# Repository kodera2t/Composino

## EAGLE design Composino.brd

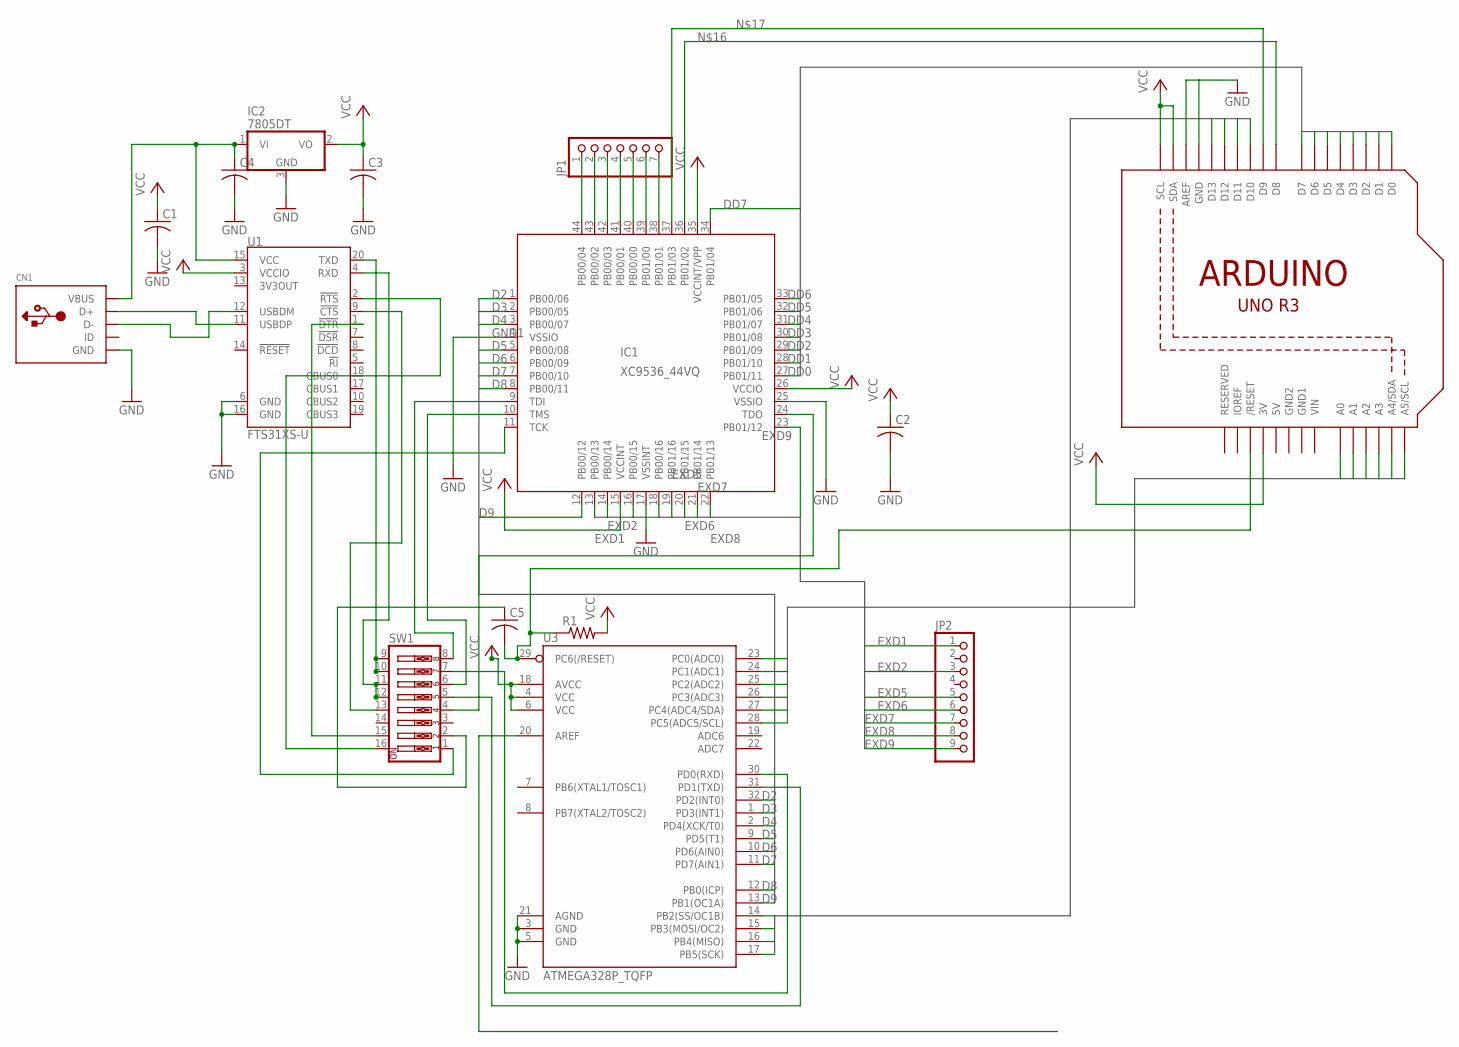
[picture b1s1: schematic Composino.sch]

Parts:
C1, C2, C3, C4, C5: C-USC0603K; C0603K
CN1: USBMINIBLARGE; USB-MINIB_LARGER
IC1: XC9536_44VQ; SQFP-S-10X10-44
IC2: 7805DT; TO252
JP1: HEADER-1X7; 1X07_OVAL
JP2: HEADER-1X9; 1X09_OVAL
R1: R-US_R0603; R0603
SW1: SW_DIP-8-SMT-HALFSIZE; DIPSWITCH-08-50MIL
U1: FTS31XS-U; SSOP20_L
U2: ARDUINOR3NODIM; ARDUINOR3-NODIM
U3: ATMEGA328P_TQFP; TQFP32-08

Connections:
5V: U2.5V
A0: U2.A0, U3.23 (PC0(ADC0))
A1: U2.A1, U3.24 (PC1(ADC1))
A2: U2.A2, U3.25 (PC2(ADC2))
A3: U2.A3, U3.26 (PC3(ADC3))
A4: U2.A4 (A4/SDA), U3.27 (PC4(ADC4/SDA))
A5: U2.A5 (A5/SCL), U3.28 (PC5(ADC5/SCL))
D2: IC1.1 (PB00/06), U3.32 (PD2(INT0))
D3: IC1.2 (PB00/05), U3.1 (PD3(INT1))
D4: IC1.3 (PB00/07), U3.2 (PD4(XCK/T0))
D5: IC1.5 (PB00/08), U3.9 (PD5(T1))
D6: IC1.6 (PB00/09), U3.10 (PD6(AIN0))
D7: IC1.7 (PB00/10), U3.11 (PD7(AIN1))
D8: IC1.8 (PB00/11), U3.12 (PB0(ICP))
D9: IC1.12 (PB00/12), U3.13 (PB1(OC1A))
D10: U2.D10, U3.14 (PB2(SS/OC1B))
D11: U2.D11, U3.15 (PB3(MOSI/OC2))
D12: U2.D12, U3.16 (PB4(MISO))
D13: U2.D13, U3.17 (PB5(SCK))
DD0: IC1.27 (PB01/11), U2.D0
DD1: IC1.28 (PB01/10), U2.D1
DD2: IC1.29 (PB01/09), U2.D2
DD3: IC1.30 (PB01/08), U2.D3
DD4: IC1.31 (PB01/07), U2.D4
DD5: IC1.32 (PB01/06), U2.D5
DD6: IC1.33 (PB01/05), U2.D6
DD7: IC1.34 (PB01/04), U2.D7
EXD1: IC1.13 (PB00/13), JP2.1
EXD2: IC1.14 (PB00/14), JP2.3
EXD3: IC1.16 (PB00/15)
EXD4: IC1.18 (PB00/16)
EXD5: IC1.19 (PB01/16), JP2.5
EXD6: IC1.20 (PB01/15), JP2.6
EXD7: IC1.21 (PB01/14), JP2.7
EXD8: IC1.22 (PB01/13), JP2.8
EXD9: IC1.23 (PB01/12), JP2.9
GND1: C1.2, C2.2, C3.2, C4.2, CN1.GND, IC1.4 (VSSIO), IC1.17 (VSSINT), IC1.25 (VSSIO), IC2.3 (GND), U1.6 (GND), U1.16 (GND), U2.AREF, U2.GND, U2.GND1, U2.GND2, U3.3 (GND), U3.5 (GND), U3.21 (AGND)
unnamed: CN1.D+, U1.11 (USBDP)
unnamed: CN1.D-, U1.12 (USBDM)
unnamed: C4.1, CN1.VBUS, IC2.1 (VI), U1.15 (VCC)
unnamed: IC1.9 (TDI), SW1.8
unnamed: IC1.10 (TMS), SW1.6
unnamed: SW1.16, U1.2 (!RTS)
unnamed: IC1.24 (TDO), SW1.4
unnamed: SW1.9, SW1.10, U1.20 (TXD)
unnamed: SW1.7, U3.30 (PD0(RXD))
unnamed: SW1.11, SW1.12, U1.4 (RXD)
unnamed: SW1.15, U1.1 (!DTR)
unnamed: SW1.5, U3.31 (PD1(TXD))
unnamed: SW1.13, U1.9 (!CTS)
unnamed: C5.2, R1.1, U2.RESET (/RESET), U3.29 (PC6(/RESET))
unnamed: C5.1, SW1.2
unnamed: IC1.36 (PB01/02), U2.D8
unnamed: IC1.37 (PB01/03), U2.D9
unnamed: IC1.38 (PB01/01), JP1.7
unnamed: IC1.39 (PB01/00), JP1.6
unnamed: IC1.40 (PB00/00), JP1.5
unnamed: IC1.41 (PB00/01), JP1.4
unnamed: IC1.42 (PB00/03), JP1.3
unnamed: IC1.43 (PB00/02), JP1.2
unnamed: IC1.44 (PB00/04), JP1.1
unnamed: IC1.11 (TCK), SW1.1
VCC: C1.1, C2.1, C3.1, IC1.15 (VCCINT), IC1.26 (VCCIO), IC1.35 (VCCINT/VPP), IC2.2 (VO), R1.2, U1.3 (VCCIO), U2.3V, U2.SCL, U2.SDA, U3.4 (VCC), U3.6 (VCC), U3.18 (AVCC)
VIN: U2.VIN

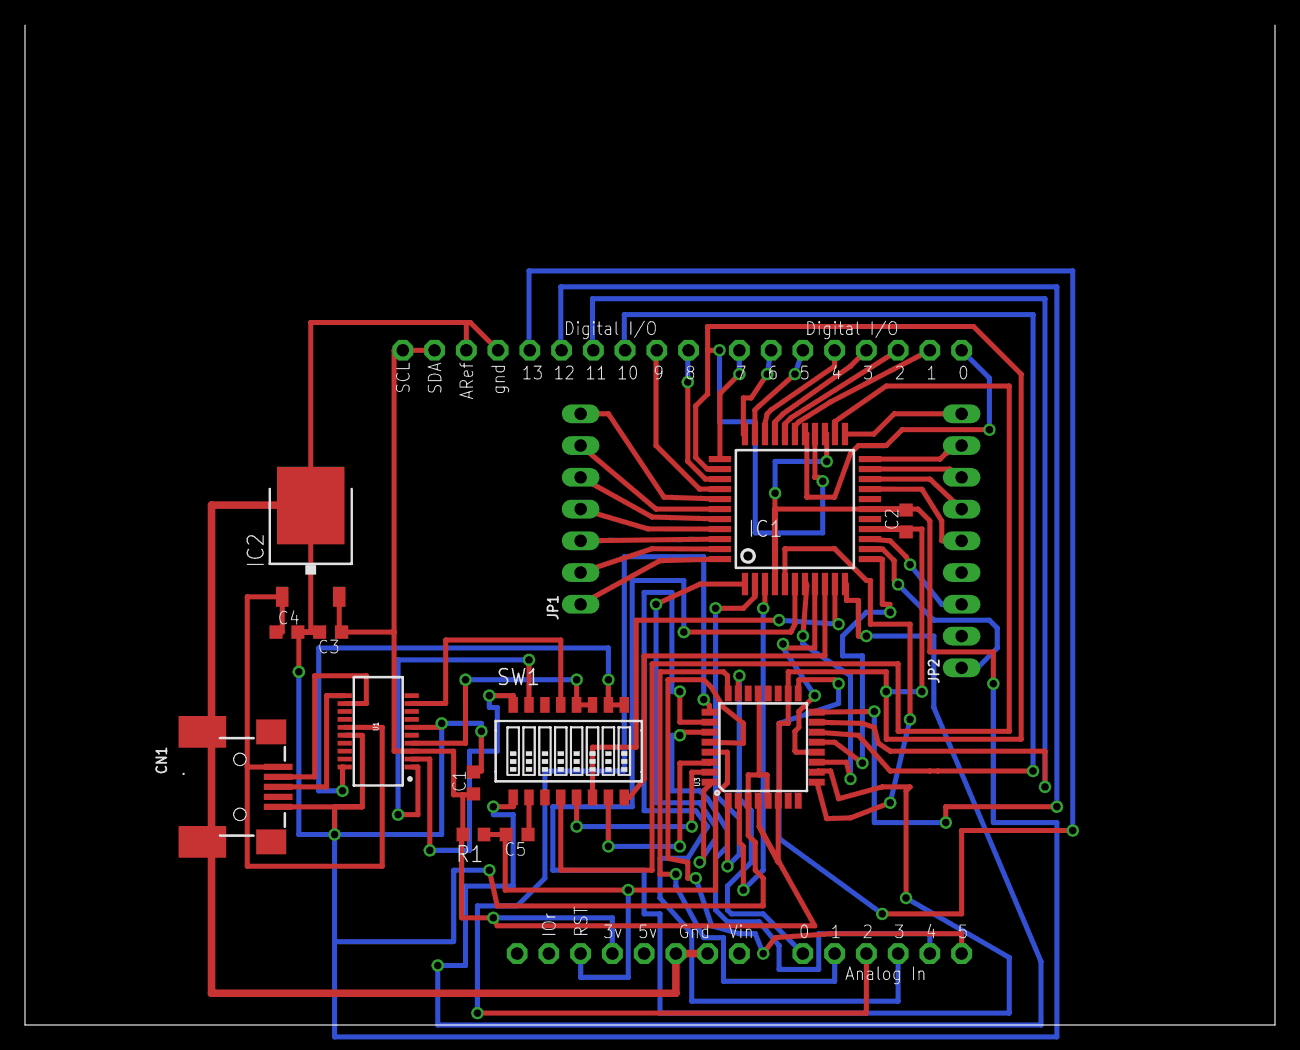
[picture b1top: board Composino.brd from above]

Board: 2 copper layers, 100.0 x 80.0 mm, 15 parts (0 on the bottom side), 60 nets.

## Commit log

2016-01-31 initial submission

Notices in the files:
parts and their libraries:
OLED_mod: This work is placed in the public domain, and may be freely used for commercial and non-commercial work with the following conditions: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
SparkFun-DigitalIC: Licensing: Creative Commons ShareAlike 4.0 International - https://creativecommons.org/licenses/by-sa/4.0
